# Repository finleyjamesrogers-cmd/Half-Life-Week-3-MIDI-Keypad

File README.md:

# Half-Life-Week-3-Drum-Pad!
This is a recreation/remake with changes version of the existing project MIDI Keypad!

### This is a complete recreation/remake with many changes of the OG project MIDI Keyboard! The major change being... It is now a DRUM PAD!

## The drum pad features:
- 8 hexagon shape exposed copper capacitive touch pads
- 4 tactile clicky buttons
- 1 Rotary Encoder
- Neopixels for the clicky buttons
- Waveshare ESP32-S3-Zero as a core processor!

## Why? 
This project was created to complete week 3 of half life - hack club!
I wanted this to be something that I can relate to more and since that is drumming I decided why not, lets make a drum pad.

## Project Status
The project is fully complete and comes with all the KiCad files, the production files, the basic code, the BOM and this readme!

## EYE CANDY!

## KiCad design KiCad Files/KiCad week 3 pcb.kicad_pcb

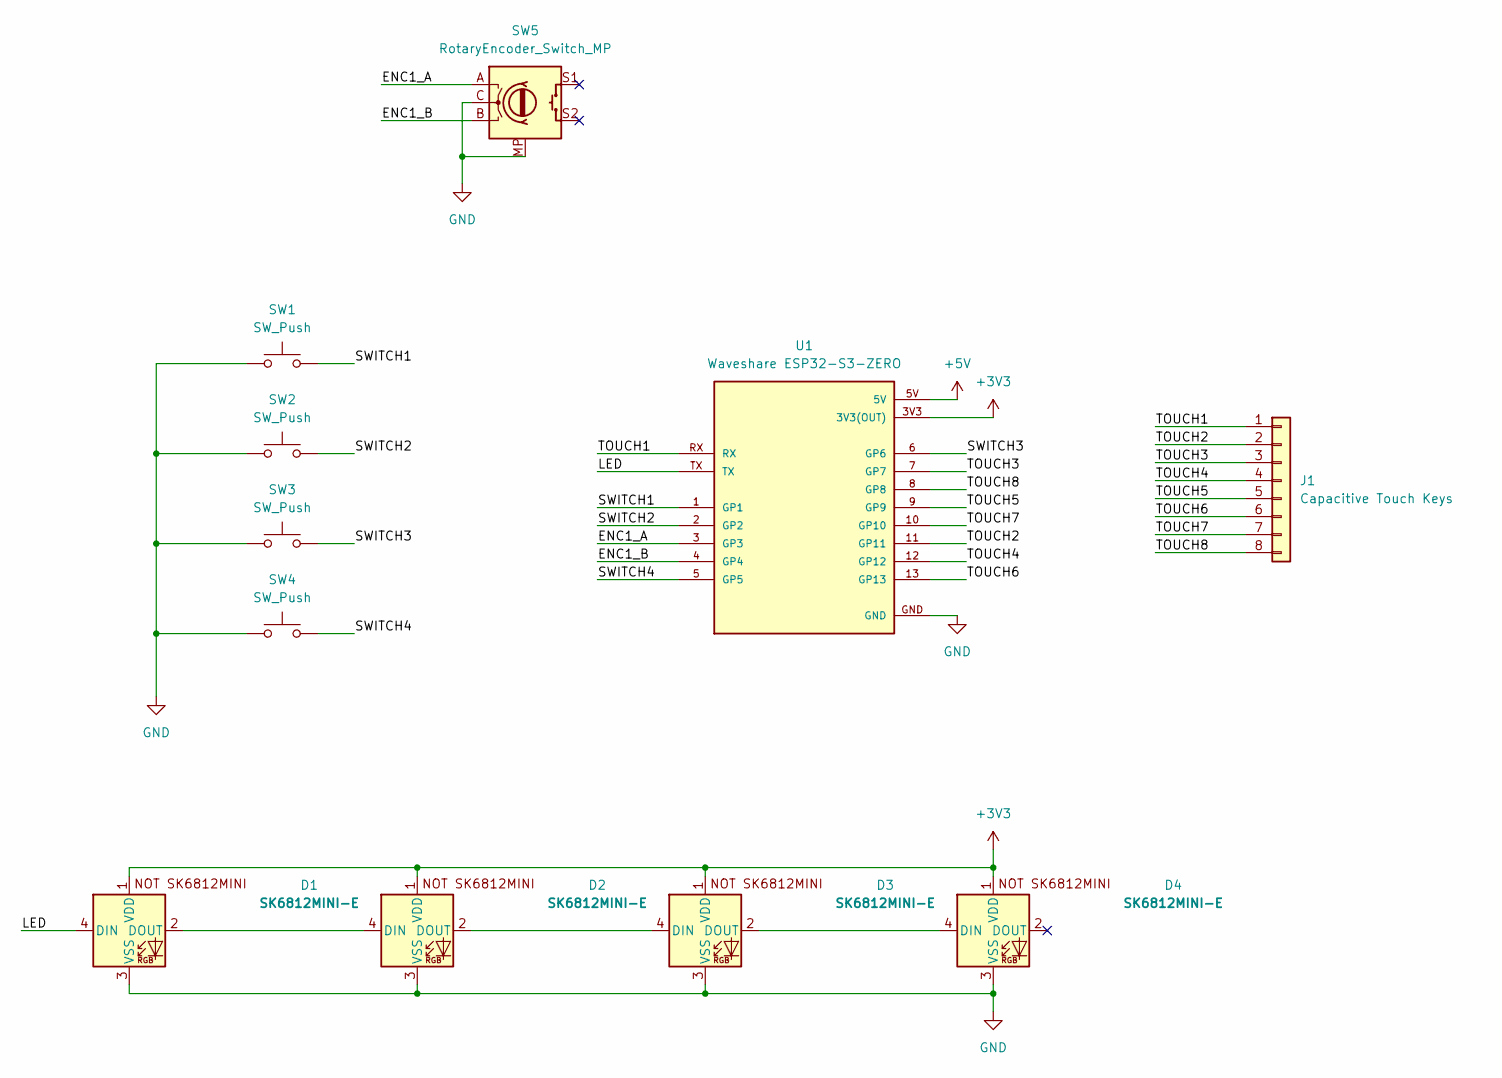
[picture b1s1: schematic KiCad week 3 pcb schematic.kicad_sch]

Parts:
D1, D2, D3, D4: SK6812MINI-E; LED_SK6812MINI-E_3.2x2.8mm_P1.5mm_ReverseMount
J1: Capacitive Touch Keys; 8x hex keys
SW1, SW2, SW3, SW4: SW_Push; Kailh Choc Low-Profile Switches
SW5: RotaryEncoder_Switch_MP; RotaryEncoder_Alps_EC11E-Switch_Vertical_H20mm_CircularMoun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
U1: Waveshare ESP32-S3-ZERO; Waveshare ESP32-S3-Zero; PARTREV NA

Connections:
+3V3: D1.1 (VDD), D2.1 (VDD), D3.1 (VDD), D4.1 (VDD), U1.3V3 (3V3(OUT))
+5V: U1.5V
/ENC1_A: SW5.A, U1.3 (GP3)
/ENC1_B: SW5.B, U1.4 (GP4)
/LED: D1.4 (DIN), U1.TX
/SWITCH1: SW1.2, U1.1 (GP1)
/SWITCH2: SW2.2, U1.2 (GP2)
/SWITCH3: SW3.2, U1.6 (GP6)
/SWITCH4: SW4.2, U1.5 (GP5)
/TOUCH1: J1.1, U1.RX
/TOUCH2: J1.2, U1.11 (GP11)
/TOUCH3: J1.3, U1.7 (GP7)
/TOUCH4: J1.4, U1.12 (GP12)
/TOUCH5: J1.5, U1.9 (GP9)
/TOUCH6: J1.6, U1.13 (GP13)
/TOUCH7: J1.7, U1.10 (GP10)
/TOUCH8: J1.8, U1.8 (GP8)
GND: D1.3 (VSS), D2.3 (VSS), D3.3 (VSS), D4.3 (VSS), SW1.1, SW2.1, SW3.1, SW4.1, SW5.C, SW5.MP, U1.GND
unnamed: D1.2 (DOUT), D2.4 (DIN)
unnamed: D2.2 (DOUT), D3.4 (DIN)
unnamed: D3.2 (DOUT), D4.4 (DIN)

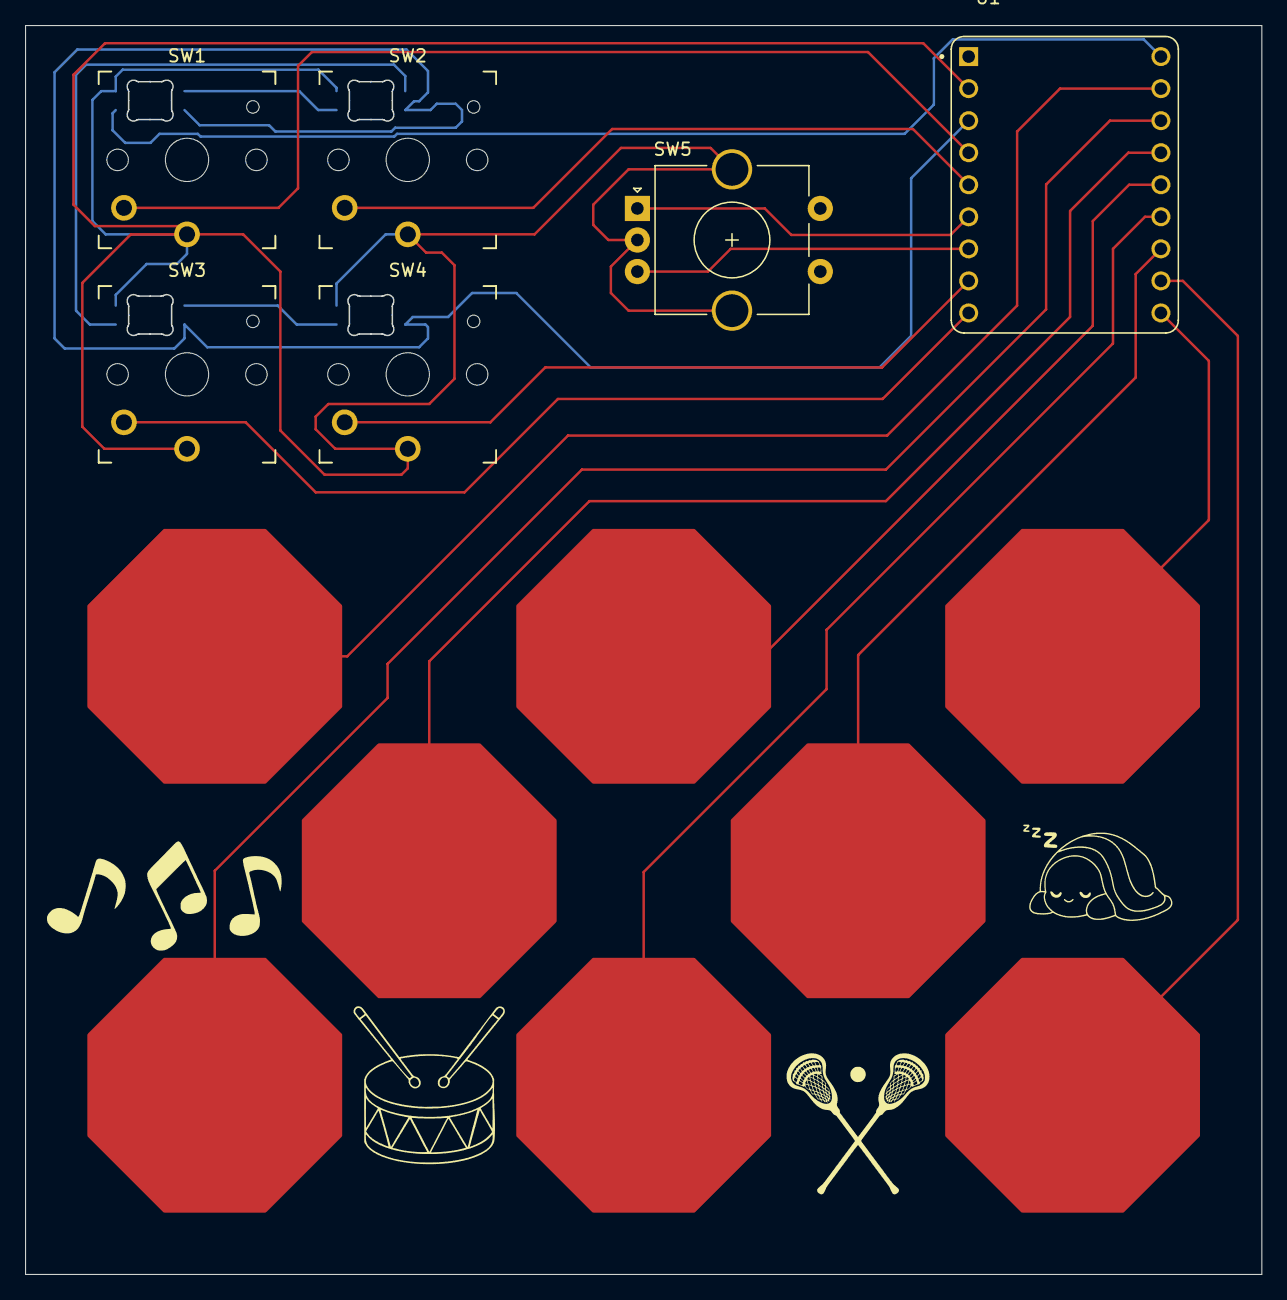
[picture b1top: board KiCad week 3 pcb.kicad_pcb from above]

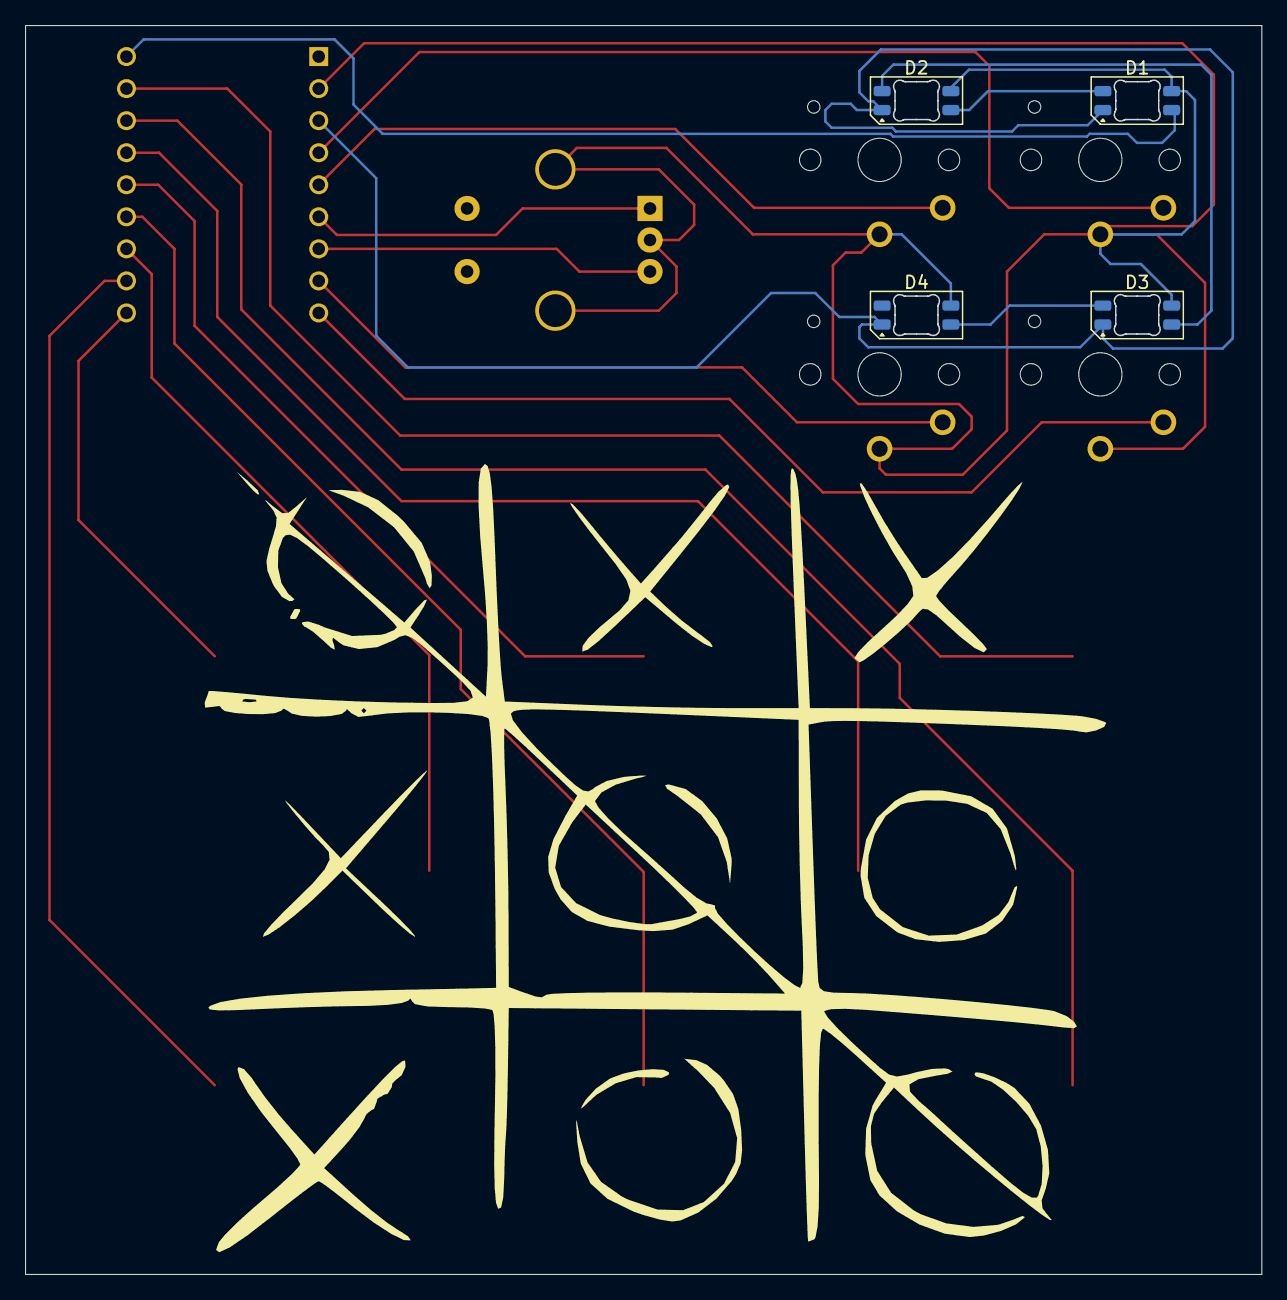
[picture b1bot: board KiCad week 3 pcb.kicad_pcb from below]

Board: 2 copper layers, 98.0 x 99.0 mm, 11 parts (4 on the bottom side), 20 nets.
